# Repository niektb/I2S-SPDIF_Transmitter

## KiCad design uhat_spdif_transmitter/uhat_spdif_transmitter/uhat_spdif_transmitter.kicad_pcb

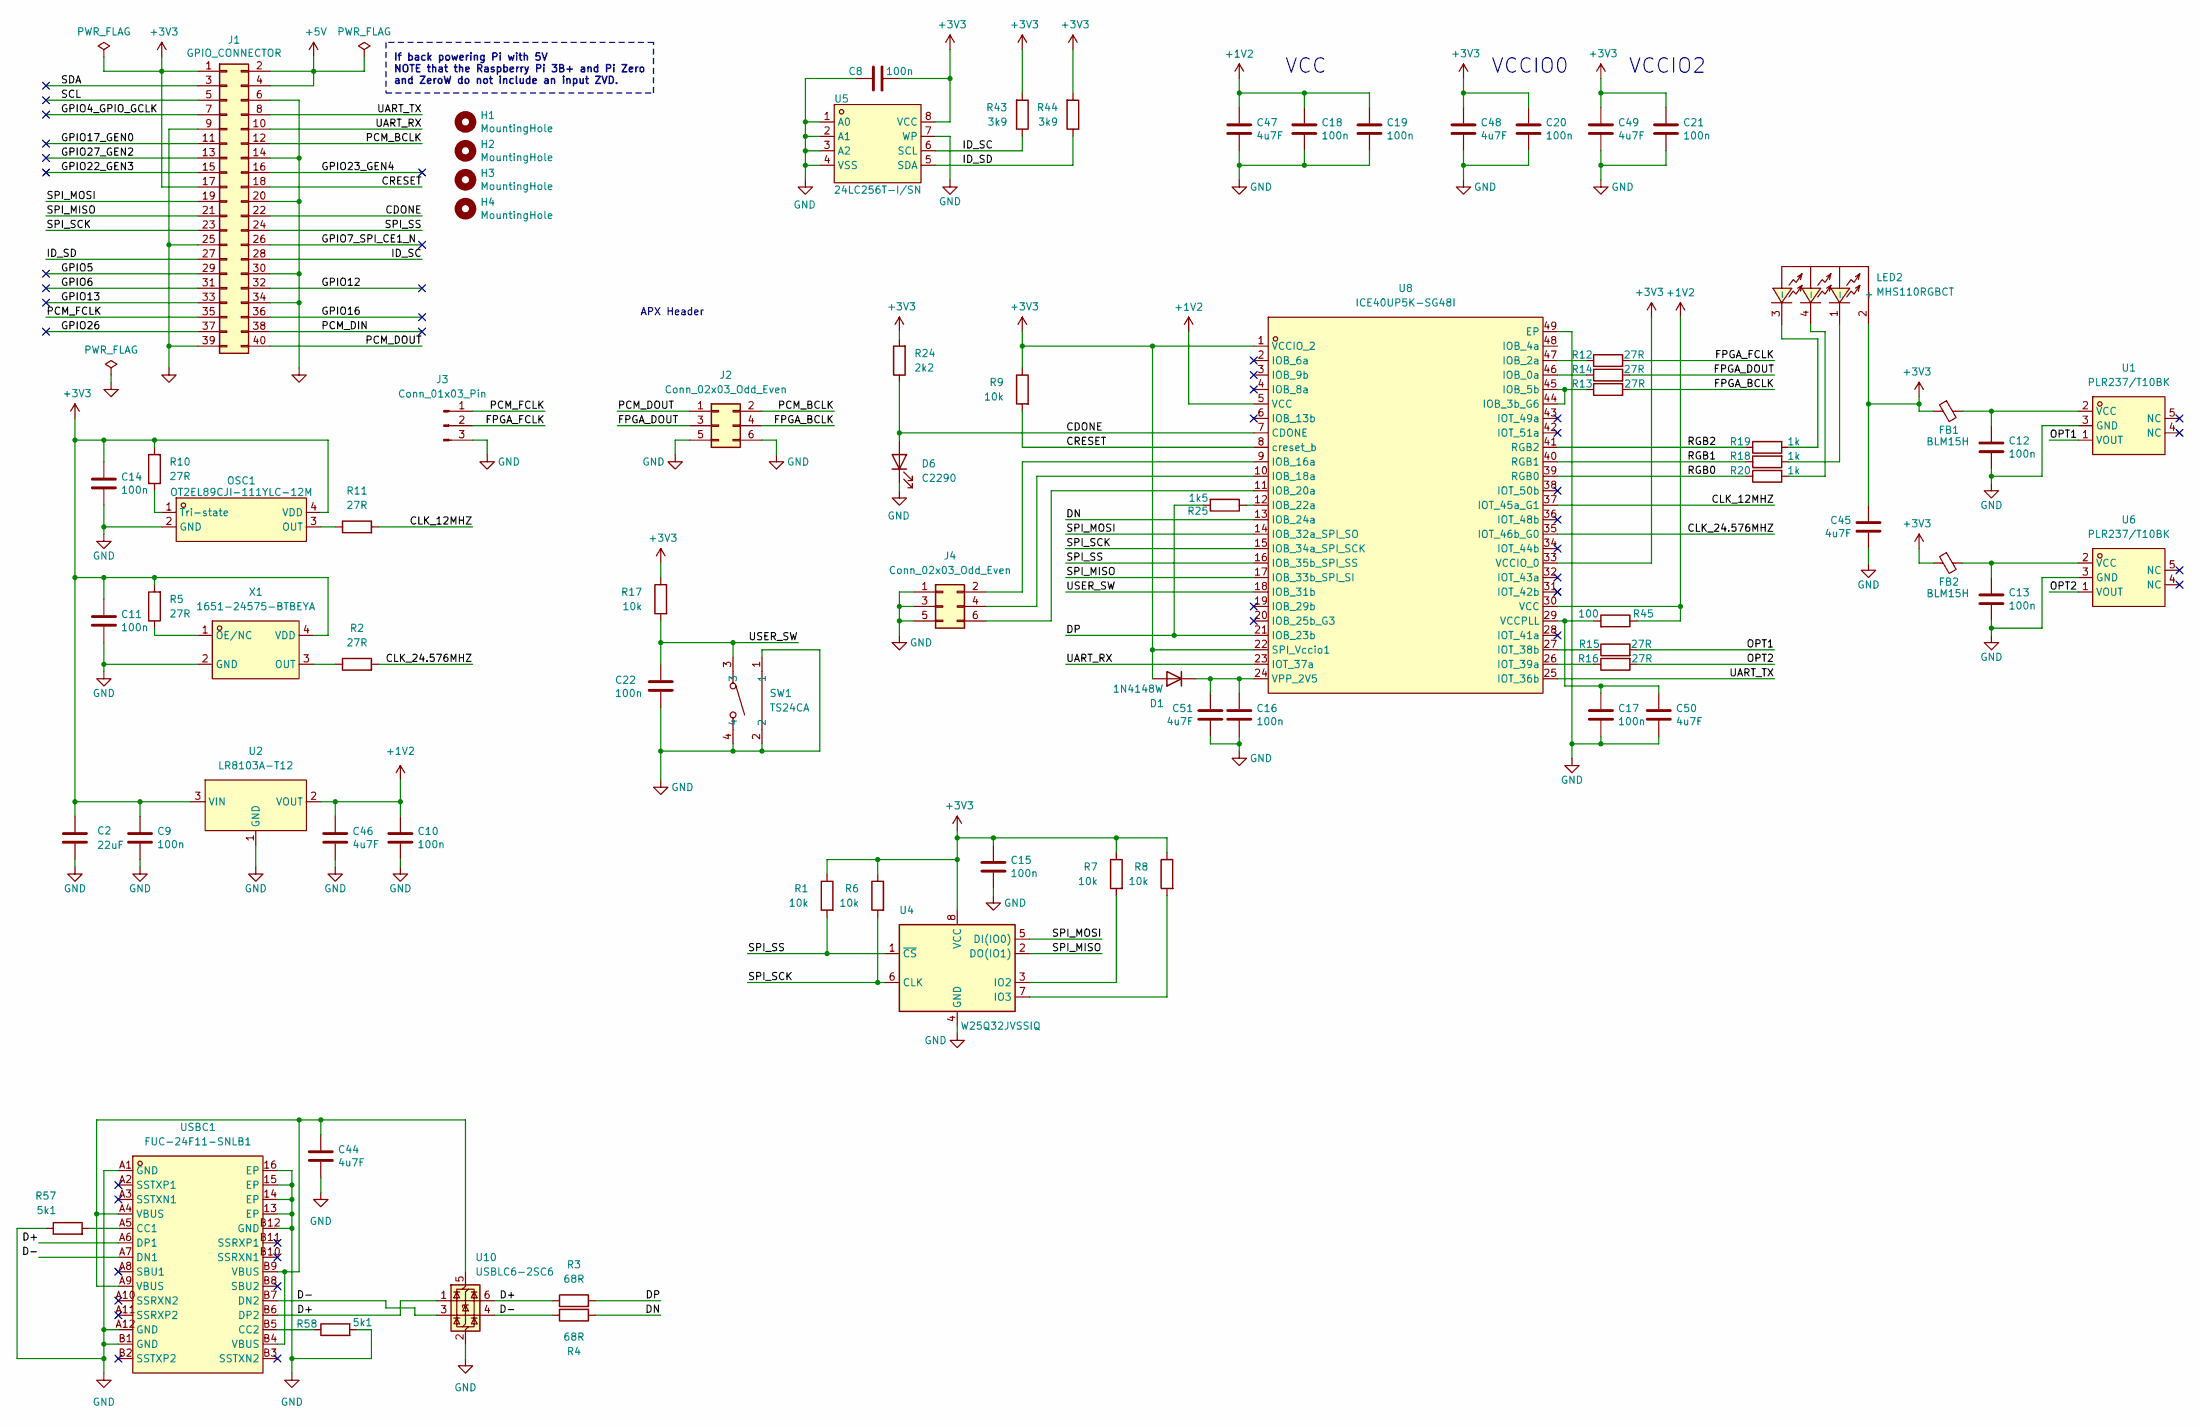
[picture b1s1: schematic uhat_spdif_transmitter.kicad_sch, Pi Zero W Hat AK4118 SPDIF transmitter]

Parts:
C2: 22uF; C_1206_3216Metric_Pad1.33x1.80mm_HandSolder
C8, C9, C10, C11, C12, C13, C14, C15, C16, C17, C18, C19, C20, C21, C22: 100n; C_0402_1005Metric
C44, C45, C46, C47, C48, C49, C50, C51: 4u7F; C_0603_1608Metric_Pad1.08x0.95mm_HandSolder
D1: 1N4148W; D_SOD-123
D6: C2290; LED_0805_2012Metric
FB1, FB2: BLM15H; L_0402_1005Metric
H1, H2, H3, H4: MountingHole; MountingHole_2.7mm_M2.5_uHAT_RPi
J1: GPIO_CONNECTOR; PinSocket_2x20_P2.54mm_Vertical_Centered_Anchor
J2, J4: Conn_02x03_Odd_Even; PinHeader_2x03_P2.54mm_Vertical
J3: Conn_01x03_Pin; PinHeader_1x03_P2.54mm_Vertical
LED2: MHS110RGBCT; LED-ARRAY-SMD_MHS110RGBCT; LCSC Part C389528
OSC1: OT2EL89CJI-111YLC-12M; OSC-SMD_4P-L3.2-W2.5-BL; LCSC Part C5280582
R1, R6, R7, R8, R9, R17: 10k; R_0402_1005Metric
R2, R5, R10, R11, R12, R13, R14, R15, R16: 27R; R_0402_1005Metric_Pad0.72x0.64mm_HandSolder
R3, R4: 68R; R_0402_1005Metric_Pad0.72x0.64mm_HandSolder
R18, R19, R20: 1k; R_0402_1005Metric_Pad0.72x0.64mm_HandSolder
R24: 2k2; R_0603_1608Metric_Pad0.98x0.95mm_HandSolder
R25: 1k5; R_0603_1608Metric_Pad0.98x0.95mm_HandSolder
R43, R44: 3k9; R_0603_1608Metric_Pad0.98x0.95mm_HandSolder
R45: 100; R_0603_1608Metric_Pad0.98x0.95mm_HandSolder
R57, R58: 5k1; R_0603_1608Metric_Pad0.98x0.95mm_HandSolder
SW1: TS24CA; SW-SMD_TS24CA; LCSC Part C393942
U1, U6: PLR237/T10BK; OPTO-TH_PLR237-T10BK; LCSC Part C17427482
U2: LR8103A-T12; SOT-23-3_L2.9-W1.6-P1.90-LS2.8-BR; LCSC Part C7501644
U4: W25Q32JVSSIQ; SOIC-8_5.3x5.3mm_P1.27mm
U5: 24LC256T-I/SN; SOIC-8_L4.9-W3.9-P1.27-LS6.0-BL; LCSC Part C5458
U8: ICE40UP5K-SG48I; QFN-48_L7.0-W7.0-P0.50-TL-EP5.4-1; LCSC Part C2678152
U10: USBLC6-2SC6; SOT-23-6
USBC1: FUC-24F11-SNLB1; USB-C-SMD_C67380; LCSC Part C67380
X1: 1651-24575-BTBEYA; OSC-SMD_4P-L2.5-W2.0-BL; LCSC Part C3003263

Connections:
+1V2: C10.1, C18.1, C19.1, C46.1, C47.1, R45.1, U2.2 (VOUT), U8.5 (VCC), U8.30 (VCC)
+3V3: C2.1, C8.2, C9.1, C11.1, C14.1, C15.1, C20.1, C21.1, C45.1, C48.1, C49.1, D1.2 (A), FB1.1, FB2.1, J1.1, J1.17, LED2.2 (+), OSC1.4 (VDD), R1.1, R5.2, R6.1, R7.1, R8.1, R9.1, R10.2, R17.1, R24.2, R43.2, R44.2, U2.3 (VIN), U4.8 (VCC), U5.8 (VCC), U8.1 (VCCIO_2), U8.22 (SPI_Vccio1), U8.33 (VCCIO_0), X1.4 (VDD)
+5V: J1.2, J1.4
/CDONE: D6.2 (A), J1.22, R24.1, U8.7 (CDONE)
/CLK_12MHZ: R11.2, U8.37 (IOT_45a_G1)
/CLK_24.576MHZ: R2.2, U8.35 (IOT_46b_G0)
/CRESET: J1.18, R9.2, U8.8 (creset_b)
/D+: R3.1, U10.1 (I/O1), U10.6 (I/O1), USBC1.A6 (DP1), USBC1.B6 (DP2)
/D-: R4.1, U10.3 (I/O2), U10.4 (I/O2), USBC1.A7 (DN1), USBC1.B7 (DN2)
/DN: R4.2, U8.13 (IOB_24a)
/DP: R3.2, R25.2, U8.21 (IOB_23b)
/FPGA_BCLK: J2.4, R13.2
/FPGA_DOUT: J2.3, R14.2
/FPGA_FCLK: J3.2, R12.2
/GPIO4_GPIO_GCLK: J1.7
/GPIO5: J1.29
/GPIO6: J1.31
/GPIO7_SPI_CE1_N: J1.26
/GPIO12: J1.32
/GPIO13: J1.33
/GPIO16: J1.36
/GPIO17_GEN0: J1.11
/GPIO22_GEN3: J1.15
/GPIO23_GEN4: J1.16
/GPIO26: J1.37
/GPIO27_GEN2: J1.13
/ID_SC: J1.28, R43.1, U5.6 (SCL)
/ID_SD: J1.27, R44.1, U5.5 (SDA)
/OPT1: R15.2, U1.1 (VOUT)
/OPT2: R16.2, U6.1 (VOUT)
/PCM_BCLK: J1.12, J2.2
/PCM_DIN: J1.38
/PCM_DOUT: J1.40, J2.1
/PCM_FCLK: J1.35, J3.1
/RGB0: R20.1, U8.39 (RGB0)
/RGB1: R18.1, U8.40 (RGB1)
/RGB2: R19.1, U8.41 (RGB2)
/SCL: J1.5
/SDA: J1.3
/SPI_MISO: J1.21, U4.2 (DO(IO1)), U8.17 (IOB_33b_SPI_SI)
/SPI_MOSI: J1.19, U4.5 (DI(IO0)), U8.14 (IOB_32a_SPI_SO)
/SPI_SCK: J1.23, R6.2, U4.6 (CLK), U8.15 (IOB_34a_SPI_SCK)
/SPI_SS: J1.24, R1.2, U4.1 (~CS), U8.16 (IOB_35b_SPI_SS)
/UART_RX: J1.10, U8.23 (IOT_37a)
/UART_TX: J1.8, U8.25 (IOT_36b)
/USER_SW: C22.1, R17.2, SW1.3, U8.18 (IOB_31b)
GND: C2.2, C8.1, C9.2, C10.2, C11.2, C12.2, C13.2, C14.2, C15.2, C16.2, C17.2, C18.2, C19.2, C20.2, C21.2, C22.2, C44.2, C45.2, C46.2, C47.2, C48.2, C49.2, C50.2, C51.2, D6.1 (K), J1.6, J1.9, J1.14, J1.20, J1.25, J1.30, J1.34, J1.39, J2.5, J2.6, J3.3, J4.1, J4.3, J4.5, OSC1.2 (GND), R57.1, R58.2, SW1.1, SW1.2, SW1.4, U1.3 (GND), U2.1 (GND), U4.4 (GND), U5.1 (A0), U5.2 (A1), U5.3 (A2), U5.4 (VSS), U5.7 (WP), U6.3 (GND), U8.49 (EP), U10.2 (GND), USBC1.13 (EP), USBC1.14 (EP), USBC1.15 (EP), USBC1.16 (EP), USBC1.A1 (GND), USBC1.A12 (GND), USBC1.B1 (GND), USBC1.B12 (GND), X1.2 (GND)
unnamed: C16.1, C51.1, D1.1 (K), U8.24 (VPP_2V5)
unnamed: J4.2, U8.9 (IOB_16a)
unnamed: J4.4, U8.10 (IOB_18a)
unnamed: J4.6, U8.11 (IOB_20a)
unnamed: LED2.1 (-), R18.2
unnamed: LED2.3 (-), R19.2
unnamed: LED2.4 (-), R20.2
unnamed: OSC1.3 (OUT), R11.1
unnamed: OSC1.1 (Tri-state), R10.1
unnamed: C12.1, FB1.2, U1.2 (VCC)
unnamed: R7.2, U4.3 (IO2)
unnamed: R8.2, U4.7 (IO3)
unnamed: C13.1, FB2.2, U6.2 (VCC)
unnamed: R14.1, U8.46 (IOB_0a)
unnamed: R12.1, U8.47 (IOB_2a)
unnamed: R13.1, U8.44 (IOB_3b_G6), U8.45 (IOB_5b)
unnamed: R25.1, U8.12 (IOB_22a)
unnamed: R15.1, U8.27 (IOT_38b)
unnamed: R16.1, U8.26 (IOT_39a)
unnamed: C17.1, C50.1, R45.2, U8.29 (VCCPLL)
unnamed: C44.1, U10.5 (VBUS), USBC1.A4 (VBUS), USBC1.A9 (VBUS), USBC1.B4 (VBUS), USBC1.B9 (VBUS)
unnamed: R57.2, USBC1.A5 (CC1)
unnamed: R58.1, USBC1.B5 (CC2)
unnamed: R5.1, X1.1 (OE/NC)
unnamed: R2.1, X1.3 (OUT)

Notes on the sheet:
If back powering Pi with 5V NOTE that the Raspberry Pi 3B+ and Pi Zero and ZeroW do not include an input ZVD.
VCCIO2
APX Header
VCCIO0
VCC

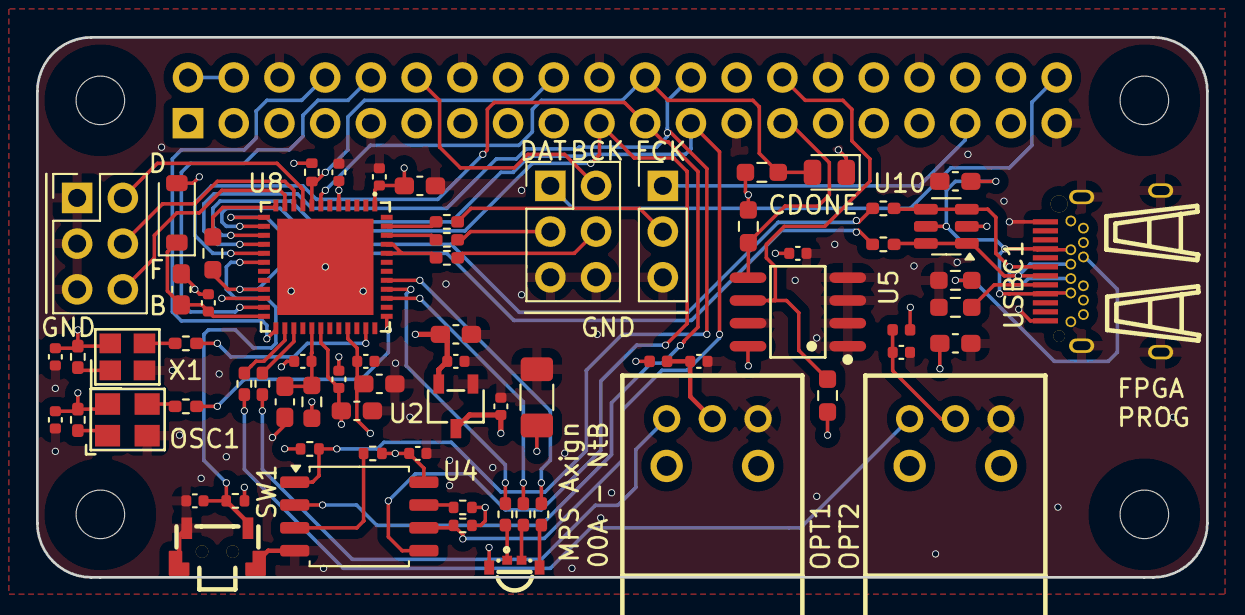
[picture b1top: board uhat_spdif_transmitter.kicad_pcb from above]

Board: 4 copper layers, 65.0 x 30.0 mm, 75 parts (1 on the bottom side), 57 nets.

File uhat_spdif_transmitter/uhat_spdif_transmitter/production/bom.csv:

Designator,Footprint,Quantity,Value,LCSC Part #
"C10, C11, C12, C13, C14, C15, C16, C17, C18, C19, C20, C21, C22, C8, C9",0402,15,100n,
C2,1206,1,22uF,
"C44, C45, C46, C47, C48, C49, C50, C51",0603,8,4u7F,
D1,D_SOD-123,1,1N4148W,
D6,0805,1,C2290,
"FB1, FB2",0402,2,BLM15H,
"H1, H2, H3, H4",MountingHole_2.7mm_M2.5_uHAT_RPi,4,MountingHole,
J1,PinSocket_2x20_P2.54mm_Vertical_Centered_Anchor,1,GPIO_CONNECTOR,
"J2, J4",PinHeader_2x03_P2.54mm_Vertical,2,Conn_02x03_Odd_Even,
J3,PinHeader_1x03_P2.54mm_Vertical,1,Conn_01x03_Pin,
LED2,LED-ARRAY-SMD_MHS110RGBCT,1,MHS110RGBCT,C389528
OSC1,OSC-SMD_4P-L3.2-W2.5-BL,1,OT2EL89CJI-111YLC-12M,C5280582
"R1, R17, R6, R7, R8, R9",0402,6,10k,
"R10, R11, R12, R13, R14, R15, R16, R2, R5",0402,9,27R,
"R18, R19, R20",0402,3,1k,
R24,0603,1,2k2,
R25,0603,1,1k5,
"R3, R4",0402,2,68R,
"R43, R44",0603,2,3k9,
R45,0603,1,100,
"R57, R58",0603,2,5k1,
SW1,SW-SMD_TS24CA,1,TS24CA,C393942
"U1, U6",OPTO-TH_PLR237-T10BK,2,PLR237/T10BK,C17427482
U10,SOT-23-6,1,USBLC6-2SC6,
U2,SOT-23-3_L2.9-W1.6-P1.90-LS2.8-BR,1,LR8103A-T12,C7501644
U4,SOIC-8_5.3x5.3mm_P1.27mm,1,W25Q32JVSSIQ,
U5,SOIC-8_L4.9-W3.9-P1.27-LS6.0-BL,1,24LC256T-I/SN,C5458
U8,QFN-48_L7.0-W7.0-P0.50-TL-EP5.4-1,1,ICE40UP5K-SG48I,C2678152
USBC1,USB-C-SMD_C67380,1,FUC-24F11-SNLB1,C67380
X1,OSC-SMD_4P-L2.5-W2.0-BL,1,1651-24575-BTBEYA,C3003263

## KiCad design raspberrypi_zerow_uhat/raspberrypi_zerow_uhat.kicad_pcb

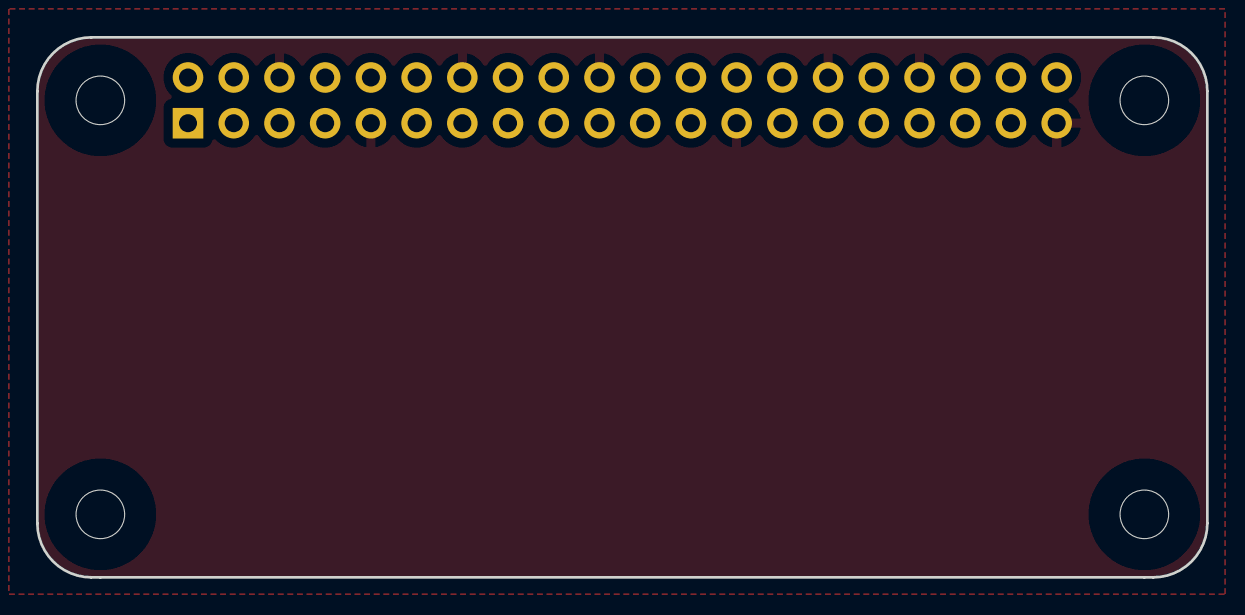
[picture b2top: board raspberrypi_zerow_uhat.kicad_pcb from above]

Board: 2 copper layers, 65.0 x 30.0 mm, 5 parts (1 on the bottom side), 3 nets, no tracks yet.

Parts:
H1, H2, H3, H4: MountingHole; MountingHole_2.7mm_M2.5_uHAT_RPi
J1: GPIO_CONNECTOR; PinSocket_2x20_P2.54mm_Vertical_Centered_Anchor

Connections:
+3V3: J1.1, J1.17
+5V: J1.2, J1.4
GND: J1.6, J1.9, J1.14, J1.20, J1.25, J1.30, J1.34, J1.39

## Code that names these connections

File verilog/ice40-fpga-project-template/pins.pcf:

set_io pin_cdone 7
set_io pin_creset 8
set_io pin_i2s_out_data 9
set_io pin_i2s_out_fclk 10
set_io pin_i2s_out_bclk 11
set_io pin_usb_pu 12
set_io pin_usb_dn 13
set_io pin_spi_mosi 14
set_io pin_spi_sck 15
set_io pin_spi_ss 16
set_io pin_spi_miso 17
set_io pin_user_sw 18
set_io pin_usb_dp 21
set_io pin_uart_rx 23
set_io pin_uart_tx 25
set_io pin_opt2 26
set_io pin_opt1 27
set_io pin_clk_24m576hz 35
set_io pin_clk_12mhz 37
set_io pin_rgb0 39
set_io pin_rgb1 40
set_io pin_rgb2 41
set_io pin_i2s_bclk_pll 44
set_io pin_i2s_bclk 45
set_io pin_i2s_data 46
set_io pin_i2s_fclk 47

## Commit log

2025-06-18 work-in-progress
2025-06-18 update 3d models, component placement
2025-06-19 layout
2025-06-21 Finish routing
2025-06-23 Finish layouting
2025-06-23 Change push button, add barcode location
2025-06-23 Add fabrication files
2025-07-09 Change Optical Connector + other stuff
2025-08-02 First test with APIO
2025-08-03 Attempt at I2S receiver and SPDIF transmitter
2025-08-05 Add FIFO, add proper SPDIF encoding
2025-08-05 synthesizable, with bugs ironed out
2025-08-05 Update APIO
2025-08-06 change to 24-bit datapath
2025-08-06 Make it synthesizable
2025-08-06 Seems to build?
2025-08-07 Write to all leds, mirror optical out to I2S Out Data
2025-08-07 Fix bit order, spdif speed
2025-08-08 attempt to solve timing issues
2025-08-08 Tweak reset logic
2025-08-08 forgot SIM flag
2025-08-08 Fix incorrect pointer wraparound
2025-08-09 Add test for debouncing button
2025-08-28 Improve FCLK monitoring and reset functionality
2025-08-29 Small fixes to test bench and the way clocks are treated, new build
2025-08-29 Change LED indicator, change data_en
2025-08-29 new build
2025-08-29 Test button
2025-08-29 Refined I2S receiver with better testbench
2025-08-29 Rework SPDIF Preamble
2025-08-30 Fix bit alignment
2025-08-30 Change preamble to have polarities
2025-08-30 Revert "Rework SPDIF Preamble"
    This reverts commit ee9d6042b922ff0f00842b187d3ced640288abfe.
2025-08-31 WIP Comparison with SPDIF core
2025-09-13 Try alternative spdif_transmit module
2025-09-21 New build
2025-09-21 Don't reverse data
2025-09-21 Fix mono only?
2025-09-24 Change FIFO to use FCLK not as clk but as strobe
2025-11-15 Expose different signals to pinheader for debugginh
2025-11-15 Require more correct BCLK cycles to avoid getting out of reset poorly
2025-11-15 Change debugging signals

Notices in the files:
raspberrypi_zerow_uhat/raspberrypi_zerow_uhat.kicad_pcb:
This PCB design is licensed under MIT Open Source License.
